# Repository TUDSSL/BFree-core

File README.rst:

BFree Core: Intermittent CircuitPython
-----

This is the intermittent and untethered version of CircuitPython developed jointly by researchers at TU Delft and Northwestern University
-----------

=============

.. image:: https://s3.amazonaws.com/adafruit-circuit-python/CircuitPython_Repo_header_logo.png

|Build Status| |Doc Status| |License| |Discord|

`circuitpython.org <https://circuitpython.org>`__ \| `Get CircuitPython <#get-circuitpython>`__ \|
`Documentation <#documentation>`__ \| `Contributing <#contributing>`__ \|
`Branding <#branding>`__ \| `Differences from Micropython <#differences-from-micropython>`__ \|
`Project Structure <#project-structure>`__

**CircuitPython** is a *beginner friendly*, open source version of Python for tiny, inexpensive
computers called microcontrollers. Microcontrollers are the brains of many electronics including a
wide variety of development boards used to build hobby projects and prototypes. CircuitPython in
electronics is one of the best ways to learn to code because it connects code to reality. Simply
install CircuitPython on a supported board via drag and drop and then edit a ``code.py`` file on
the CIRCUITPY drive. The code will automatically reload. No software installs are needed besides a
text editor (we recommend `Mu <https://codewith.mu/>`_ for beginners.)

CircuitPython features unified Python core APIs and a growing list of 150+ device libraries and
drivers that work with it. These libraries also work on single board computers with regular
Python via the `Adafruit Blinka Library <https://github.com/adafruit/Adafruit_Blinka>`_.

CircuitPython is based on `MicroPython <https://micropython.org>`_. See
`below <#differences-from-micropython>`_ for differences. CircuitPython development is sponsored by
`Adafruit <https://adafruit.com>`_ and is available on their educational development boards. Please
support both MicroPython and Adafruit.

Get CircuitPython
------------------

Official binaries for all supported boards are available through
`circuitpython.org/downloads <https://circuitpython.org/downloads>`_. The site includes stable, unstable and
continuous builds. Full release notes and assets are available through
`GitHub releases <https://github.com/adafruit/circuitpython/releases>`_ as well.

Documentation
-------------

Guides and videos are available through the `Adafruit Learning
System <https://learn.adafruit.com/>`__ under the `CircuitPython
category <https://learn.adafruit.com/category/circuitpython>`__. An API
reference is also available on `Read the Docs
<http://circuitpython.readthedocs.io/en/latest/?>`__. A collection of awesome
resources can be found at `Awesome CircuitPython <https://github.com/adafruit/awesome-circuitpython>`__.

Specifically useful documentation when starting out:

- `Welcome to CircuitPython <https://learn.adafruit.com/welcome-to-circuitpython>`__
- `CircuitPython Essentials <https://learn.adafruit.com/circuitpython-essentials>`__
- `Example Code <https://github.com/adafruit/Adafruit_Learning_System_Guides/tree/master/CircuitPython_Essentials>`__

Contributing
------------

See
`CONTRIBUTING.md <https://github.com/adafruit/circuitpython/blob/master/CONTRIBUTING.md>`__
for full guidelines but please be aware that by contributing to this
project you are agreeing to the `Code of
Conduct <https://github.com/adafruit/circuitpython/blob/master/CODE_OF_CONDUCT.md>`__.
Contributors who follow the `Code of
Conduct <https://github.com/adafruit/circuitpython/blob/master/CODE_OF_CONDUCT.md>`__
are welcome to submit pull requests and they will be promptly reviewed
by project admins. Please join the
`Discord <https://adafru.it/discord>`__ too.

Branding
------------

While we are happy to see CircuitPython forked and modified, we'd appreciate it if forked releases
not use the name "CircuitPython" or the Blinka logo. "CircuitPython" means something special to
us and those who learn about it. As a result, we'd like to make sure products referring to it meet a
common set of requirements.

If you'd like to use the term "CircuitPython" and Blinka for your product here is what we ask:

* Your product is supported by the primary
  `"adafruit/circuitpython" <https://github.com/adafruit/circuitpython>`_ repo. This way we can
  update any custom code as we update the CircuitPython internals.
* Your product is listed on `circuitpython.org <https:/circuitpython.org>`__ (source
  `here <https://github.com/adafruit/circuitpython-org/>`_). This is to ensure that a user of your
  product can always download the latest version of CircuitPython from the standard place.
* Your product has a user accessible USB plug which appears as a CIRCUITPY drive when plugged in.

If you choose not to meet these requirements, then we ask you call your version of CircuitPython
something else (for example, SuperDuperPython) and not use the Blinka logo. You can say it is
"CircuitPython-compatible" if most CircuitPython drivers will work with it.

--------------

Differences from `MicroPython <https://github.com/micropython/micropython>`__
-----------------------------------------------------------------------------

CircuitPython:

-  includes ports for MicroChip SAMD21 (Commonly known as M0 in Adafruit
   product names) and SAMD51 (M4).
-  supports only SAMD21, SAMD51, and nRF52840 ports.
-  tracks MicroPython's releases (not master).
-  floats (aka decimals) are enabled for all builds.
-  error messages are translated into 10+ languages.
-  does not support concurrency within Python (including interrupts and threading). Some concurrency
   is achieved with native modules for tasks that require it such as audio file playback.

Behavior
~~~~~~~~

-  The order that files are run and the state that is shared between
   them. CircuitPython's goal is to clarify the role of each file and
   make each file independent from each other.
-  ``boot.py`` (or ``settings.py``) runs only once on start up before
   USB is initialized. This lays the ground work for configuring USB at
   startup rather than it being fixed. Since serial is not available,
   output is written to ``boot_out.txt``.
-  ``code.py`` (or ``main.py``) is run after every reload until it
   finishes or is interrupted. After it is done running, the vm and
   hardware is reinitialized. **This means you cannot read state from**
   ``code.py`` **in the REPL anymore.** CircuitPython's goal for this
   change includes reduce confusion about pins and memory being used.
-  After ``code.py`` the REPL can be entered by pressing any key. It no
   longer shares state with ``code.py`` so it is a fresh vm.
-  Autoreload state will be maintained across reload.
-  Adds a safe mode that does not run user code after a hard crash or
   brown out. The hope is that this will make it easier to fix code that
   causes nasty crashes by making it available through mass storage
   after the crash. A reset (the button) is needed after its fixed to
   get back into normal mode.
-  RGB status LED indicating CircuitPython state, and errors through a sequence of colored flashes.
-  Re-runs ``code.py`` or other main file after file system writes over USB mass storage. (Disable with
   ``samd.disable_autoreload()``)
-  Entering the REPL after the main code is finished requires a key press which enters the REPL and
   disables autoreload.
-  Main is one of these: ``code.txt``, ``code.py``, ``main.py``,
   ``main.txt``
-  Boot is one of these: ``settings.txt``, ``settings.py``, ``boot.py``,
   ``boot.txt``

API
~~~

-  Unified hardware APIs. Documented
   `on ReadTheDocs <https://circuitpython.readthedocs.io/en/latest/shared-bindings/index.html>`_.
-  API docs are rST within the C files in ``shared-bindings``.
-  No ``machine`` API.

Modules
~~~~~~~

-  No module aliasing. (``uos`` and ``utime`` are not available as
   ``os`` and ``time`` respectively.) Instead ``os``, ``time``, and
   ``random`` are CPython compatible.
-  New ``storage`` module which manages file system mounts.
   (Functionality from ``uos`` in MicroPython.)
-  Modules with a CPython counterpart, such as ``time``, ``os`` and
   ``random``, are strict
   `subsets <https://circuitpython.readthedocs.io/en/latest/shared-bindings/time/__init__.html>`__
   of their `CPython
   version <https://docs.python.org/3.4/library/time.html?highlight=time#module-time>`__.
   Therefore, code from CircuitPython is runnable on CPython but not
   necessarily the reverse.
-  tick count is available as
   `time.monotonic() <https://circuitpython.readthedocs.io/en/latest/shared-bindings/time/__init__.html#time.monotonic>`__

--------------

Project Structure
-----------------

Here is an overview of the top-level source code directories.

Core
~~~~

The core code of
`MicroPython <https://github.com/micropython/micropython>`__ is shared
amongst ports including CircuitPython:

-  ``docs`` High level user documentation in Sphinx reStructuredText
   format.
-  ``drivers`` External device drivers written in Python.
-  ``examples`` A few example Python scripts.
-  ``extmod`` Shared C code used in multiple ports' modules.
-  ``lib`` Shared core C code including externally developed libraries
   such as FATFS.
-  ``logo`` The CircuitPython logo.
-  ``mpy-cross`` A cross compiler that converts Python files to byte
   code prior to being run in MicroPython. Useful for reducing library
   size.
-  ``py`` Core Python implementation, including compiler, runtime, and
   core library.
-  ``shared-bindings`` Shared definition of Python modules, their docs
   and backing C APIs. Ports must implement the C API to support the
   corresponding module.
-  ``shared-module`` Shared implementation of Python modules that may be
   based on ``common-hal``.
-  ``tests`` Test framework and test scripts.
-  ``tools`` Various tools, including the pyboard.py module.

Ports
~~~~~

Ports include the code unique to a microcontroller line and also
variations based on the board.

-  ``atmel-samd`` Support for SAMD21 and SAMD51 based boards.
-  ``nrf`` Support for the nRF52840 based boards.
-  ``unix`` Support for UNIX. Only used for automated testing.

The remaining port directories not listed above are in the repo to maintain compatibility with the
`MicroPython <https://github.com/micropython/micropython>`__ parent project.

`back to top <#circuitpython>`__

.. |Build Status| image:: https://travis-ci.com/adafruit/circuitpython.svg?branch=master
   :target: https://travis-ci.org/adafruit/circuitpython
.. |Doc Status| image:: https://readthedocs.org/projects/circuitpython/badge/?version=latest
   :target: http://circuitpython.readthedocs.io/
.. |Discord| image:: https://img.shields.io/discord/327254708534116352.svg
   :target: https://adafru.it/discord
.. |License| image:: https://img.shields.io/badge/License-MIT-brightgreen.svg
   :target: https://choosealicense.com/licenses/mit/

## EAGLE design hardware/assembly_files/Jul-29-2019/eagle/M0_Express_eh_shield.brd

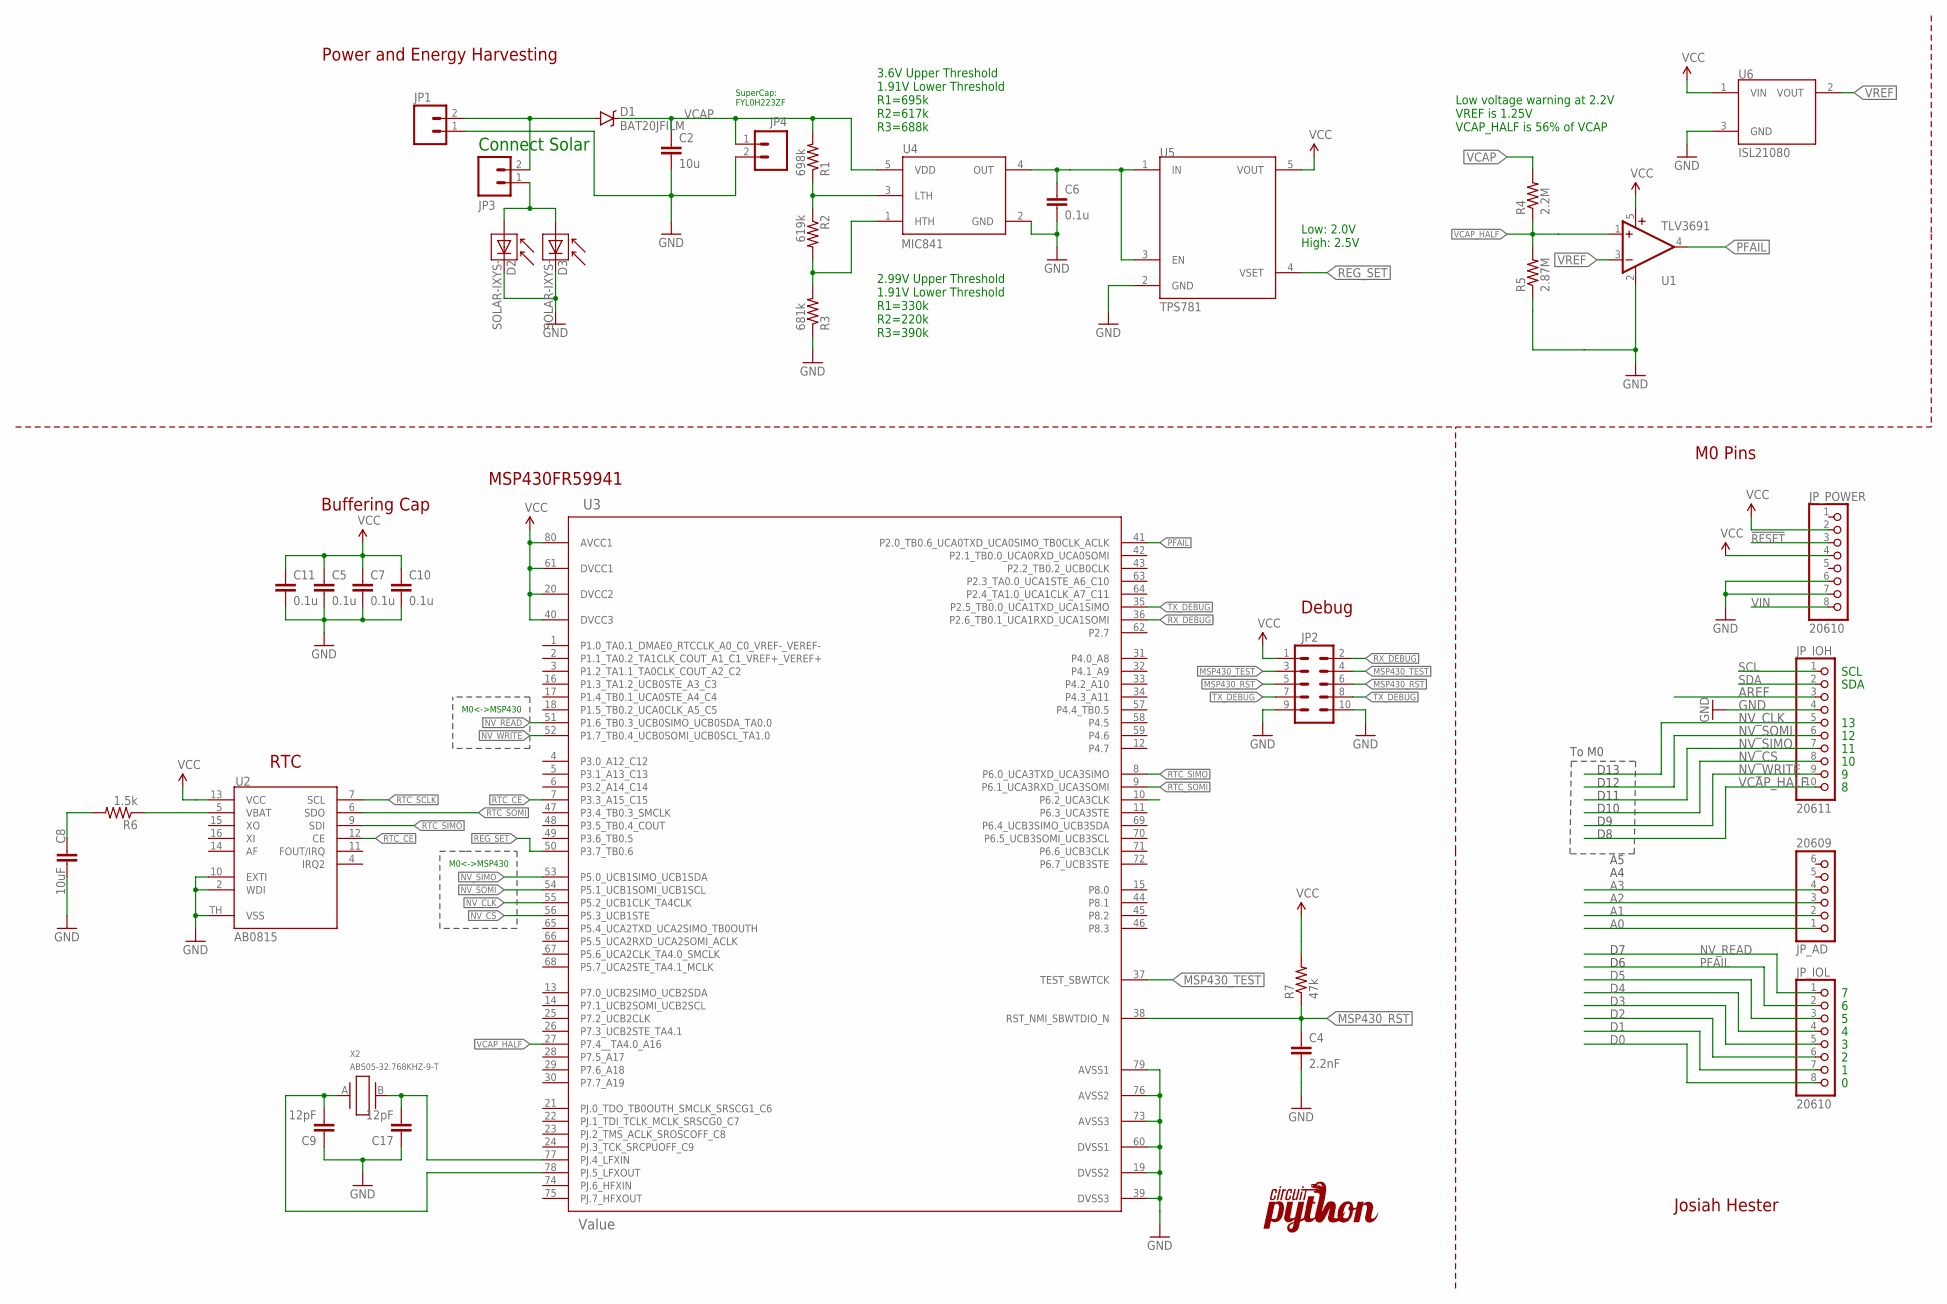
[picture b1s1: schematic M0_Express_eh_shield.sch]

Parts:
C2: 10u; 0805; DIGIKEY 1276-6456-1-ND
C4: 2.2nF; 0603; MPN 06035C222KAT2A; DIGIKEY 478-1219-1-ND
C5, C6, C7, C10, C11: 0.1u; 0603; MPN CL10B104KO8NNNC; DIGIKEY 1276-1005-1-ND
C8: 10uF; 0805; DIGIKEY 1276-6456-1-ND
C9, C17: 12pF; 0603; MPN CL10C120JB8NNNC; DIGIKEY 1276-1254-1-ND
D1: BAT20JFILM; SOD-323; DIGIKEY NSR0530HT1GOSCT-ND
D2, D3: SOLAR-IXYS-; SOLARBIT-12X1; MPN KXOB25-02X8F; DIGIKEY KXOB25-02X8F-ND
JP1, JP3: M02LOCK; 1X02_LOCK
JP2: M05X21.27MM; 2X5_1.27MM; MPN 3220-10-0100-00; DIGIKEY 1175-1627-ND
JP4: M025MM; SCREWTERMINAL-5MM-2
JP_AD: 20609; 1X06_OVALWAVE
JP_IOH: 20611; 1X10_OVALWAVE
JP_IOL: 20610; 1X08_OVALWAVE
JP_POWER: 20610; 1X08_OVALWAVE
R1: 698k; 0603; MPN RC0603FR-07698KL; DIGIKEY 311-698KHRCT-ND
R2: 619k; 0603; MPN RC0603FR-07619KL; DIGIKEY 311-619KHRCT-ND
R3: 681k; 0603; MPN RMCF0603FT681K; DIGIKEY RMCF0603FT681KCT-ND
R4: 2.2M; 0603; MPN RC0603FR-072M2L; DIGIKEY YAG3329CT-ND
R5: 2.87M; 0603; MPN RMCF0603FT2M87; DIGIKEY RMCF0603FT2M87CT-ND
R6: 1.5k; 0603; MPN CRG0603F1K5; DIGIKEY A121524CT-ND
R7: 47k; 0603; MPN CRCW060347K0JNEAC; DIGIKEY 541-4061-1-ND
U1: TLV3691; SC70-5; MPN TLV3691IDCKR; DIGIKEY 296-37910-1-ND
U2: AB0815; QFN16; MPN AB0815-T3
U3: Value; PN0080A_N; DIGIKEY 296-45561-1-ND
U4: MIC841; SC70-5; MPN MIC841HYC5-TR; DIGIKEY 576-2923-1-ND
U5: TPS781; DCK_R-PDSO-G5; DIGIKEY 296-29966-1-ND
U6: ISL21080; SOT-23; MPN ISL21080DIH312Z-TK; DIGIKEY ISL21080DIH312Z-TKTR-ND
U$1: LOGO; CIRCUITPYTHON-LOGO
X2: ABS05-32.768KHZ-9-T; ABS05; MPN ABS05-32.768KHZ-9-T

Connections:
!RESET: JP_POWER.3
A0: JP_AD.1
A1: JP_AD.2
A2: JP_AD.3
A3: JP_AD.4
AREF: JP_IOH.3
D0: JP_IOL.8
D1: JP_IOL.7
D2: JP_IOL.6
D3: JP_IOL.5
D4: JP_IOL.4
D5: JP_IOL.3
GND: C2.2, C4.2, C5.2, C6.2, C7.2, C8.2, C9.1, C10.2, C11.2, C17.1, D2.- (C), D3.- (C), JP1.1, JP2.9, JP2.10, JP4.2, JP_IOH.4, JP_POWER.6, JP_POWER.7, R3.1, R5.1, U1.2 (GND), U2.2 (WDI), U2.10 (EXTI), U2.TH (VSS), U3.19 (DVSS2), U3.39 (DVSS3), U3.60 (DVSS1), U3.73 (AVSS3), U3.76 (AVSS2), U3.79 (AVSS1), U4.2 (GND), U5.2 (GND), U6.3 (GND)
MSP430_RST: C4.1, JP2.5, JP2.6, R7.1, U3.38 (RST_NMI_SBWTDIO_N)
MSP430_TEST: JP2.3, JP2.4, U3.37 (TEST_SBWTCK)
unnamed: D1.A, JP1.2, JP3.2
unnamed: R1.1, R2.1, U4.3 (LTH)
unnamed: R2.2, R3.2, U4.1 (HTH)
unnamed: R6.1, U2.5 (VBAT)
unnamed: C17.2, U3.77 (PJ.4_LFXIN), X2.B (2)
unnamed: C9.2, U3.78 (PJ.5_LFXOUT), X2.A (1)
unnamed: C6.1, U4.4 (OUT), U5.1 (IN), U5.3 (EN)
unnamed: C8.1, R6.2
unnamed: D2.+ (A), D3.+ (A), JP3.1
NV_CLK: JP_IOH.5, U3.55 (P5.2_UCB1CLK_TA4CLK)
NV_CS: JP_IOH.8, U3.56 (P5.3_UCB1STE)
NV_READ: JP_IOL.1, U3.51 (P1.6_TB0.3_UCB0SIMO_UCB0SDA_TA0.0)
NV_SIMO: JP_IOH.7, U3.53 (P5.0_UCB1SIMO_UCB1SDA)
NV_SOMI: JP_IOH.6, U3.54 (P5.1_UCB1SOMI_UCB1SCL)
NV_WRITE: JP_IOH.9, U3.52 (P1.7_TB0.4_UCB0SOMI_UCB0SCL_TA1.0)
PFAIL: JP_IOL.2, U1.4 (OUT), U3.41 (P2.0_TB0.6_UCA0TXD_UCA0SIMO_TB0CLK_ACLK)
REG_SET: U3.50 (P3.7_TB0.6), U5.4 (VSET)
RTC_CE: U2.12 (CE), U3.7 (P3.3_A15_C15)
RTC_SCLK: U2.7 (SCL), U3.10 (P6.2_UCA3CLK)
RTC_SIMO: U2.9 (SDI), U3.8 (P6.0_UCA3TXD_UCA3SIMO)
RTC_SOMI: U2.6 (SDO), U3.9 (P6.1_UCA3RXD_UCA3SOMI)
RX_DEBUG: JP2.2, U3.36 (P2.6_TB0.1_UCA1RXD_UCA1SOMI)
SCL: JP_IOH.1
SDA: JP_IOH.2
TX_DEBUG: JP2.7, JP2.8, U3.35 (P2.5_TB0.0_UCA1TXD_UCA1SIMO)
VCAP: C2.1, D1.C, JP4.1, R1.2, R4.2, U4.5 (VDD)
VCAP_HALF: JP_IOH.10, R4.1, R5.2, U1.1 (+IN), U3.27 (P7.4__TA4.0_A16)
VCC: C5.1, C7.1, C10.1, C11.1, JP2.1, JP_POWER.2, JP_POWER.4, R7.2, U1.5 (V+), U2.13 (VCC), U3.20 (DVCC2), U3.40 (DVCC3), U3.61 (DVCC1), U3.80 (AVCC1), U5.5 (VOUT), U6.1 (VIN)
VIN: JP_POWER.8
VREF: U1.3 (-IN), U6.2 (VOUT)

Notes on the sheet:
SDA
SCL
Josiah Hester
MSP430FR59941
Power and Energy Harvesting
M0 Pins
2.99V Upper Threshold 1.91V Lower Threshold R1=330k R2=220k R3=390k
Low: 2.0V High: 2.5V
M0<->MSP430
D13
D12
D11
D10
RTC
To M0
Connect Solar
Debug
Buffering Cap
3.6V Upper Threshold 1.91V Lower Threshold R1=695k R2=617k R3=688k
Low voltage warning at 2.2V VREF is 1.25V VCAP_HALF is 56% of VCAP
SuperCap: FYL0H223ZF

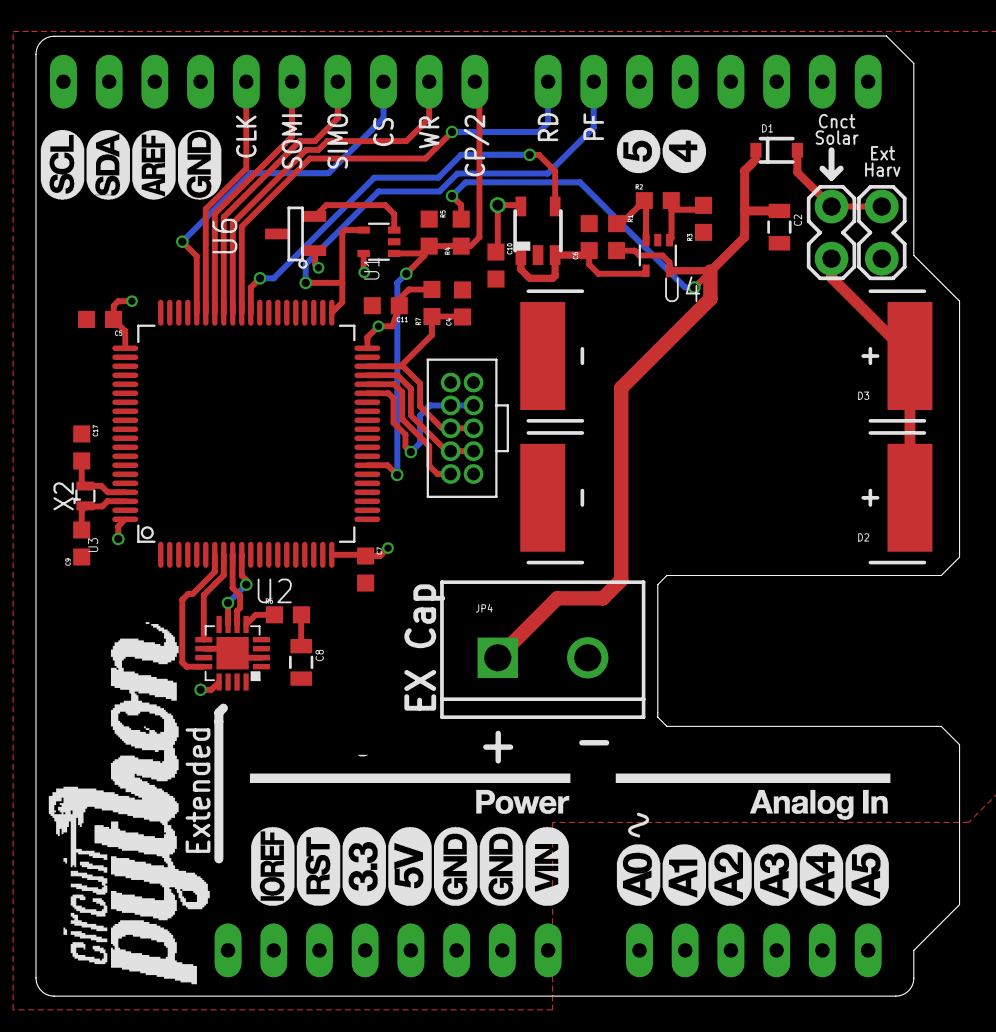
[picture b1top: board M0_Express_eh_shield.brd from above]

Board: 2 copper layers, 51.3 x 53.3 mm, 36 parts (0 on the bottom side), 30 nets.

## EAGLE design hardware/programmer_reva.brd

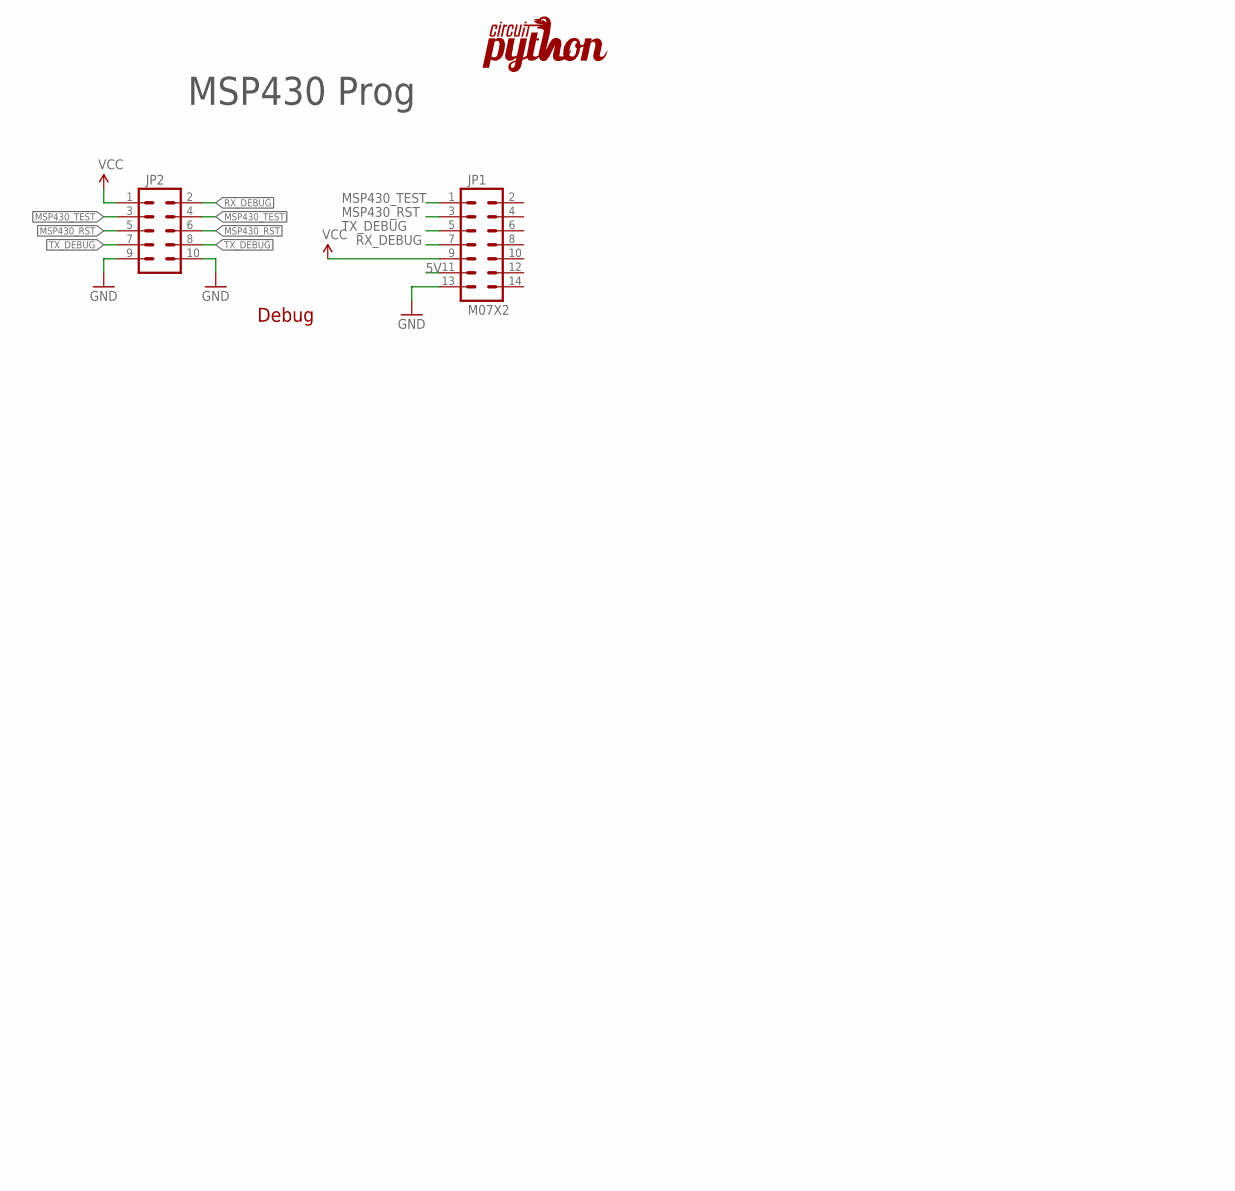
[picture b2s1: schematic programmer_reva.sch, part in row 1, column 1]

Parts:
JP1: M07X2; 2X7
JP2: M05X21.27MM; 2X5_1.27MM; DIGIKEY 1175-1627-ND
U$2: LOGO; CIRCUITPYTHON-LOGO

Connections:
5V: JP1.11
GND: JP1.13, JP2.9, JP2.10
MSP430_RST: JP1.3, JP2.5, JP2.6
MSP430_TEST: JP1.1, JP2.3, JP2.4
RX_DEBUG: JP1.7, JP2.2
TX_DEBUG: JP1.5, JP2.7, JP2.8
VCC: JP1.9, JP2.1

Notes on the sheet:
MCU, Program, Connections
EECS Northwestern University Drawn by Josiah Hester
MSP430 Prog
Debug

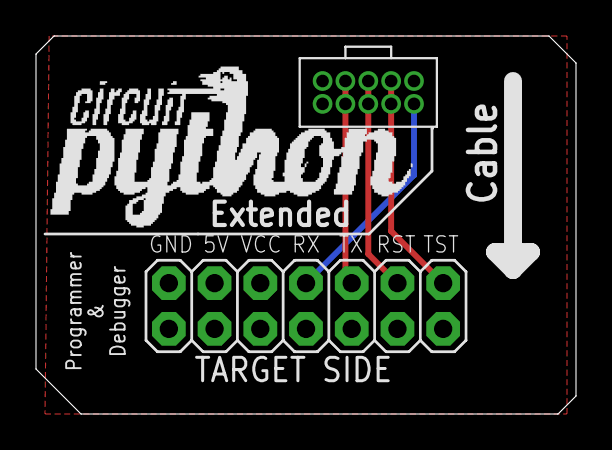
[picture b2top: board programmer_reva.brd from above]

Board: 2 copper layers, 30.0 x 21.0 mm, 4 parts (1 on the bottom side), 6 nets.

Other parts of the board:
U$1: NU-LOGO

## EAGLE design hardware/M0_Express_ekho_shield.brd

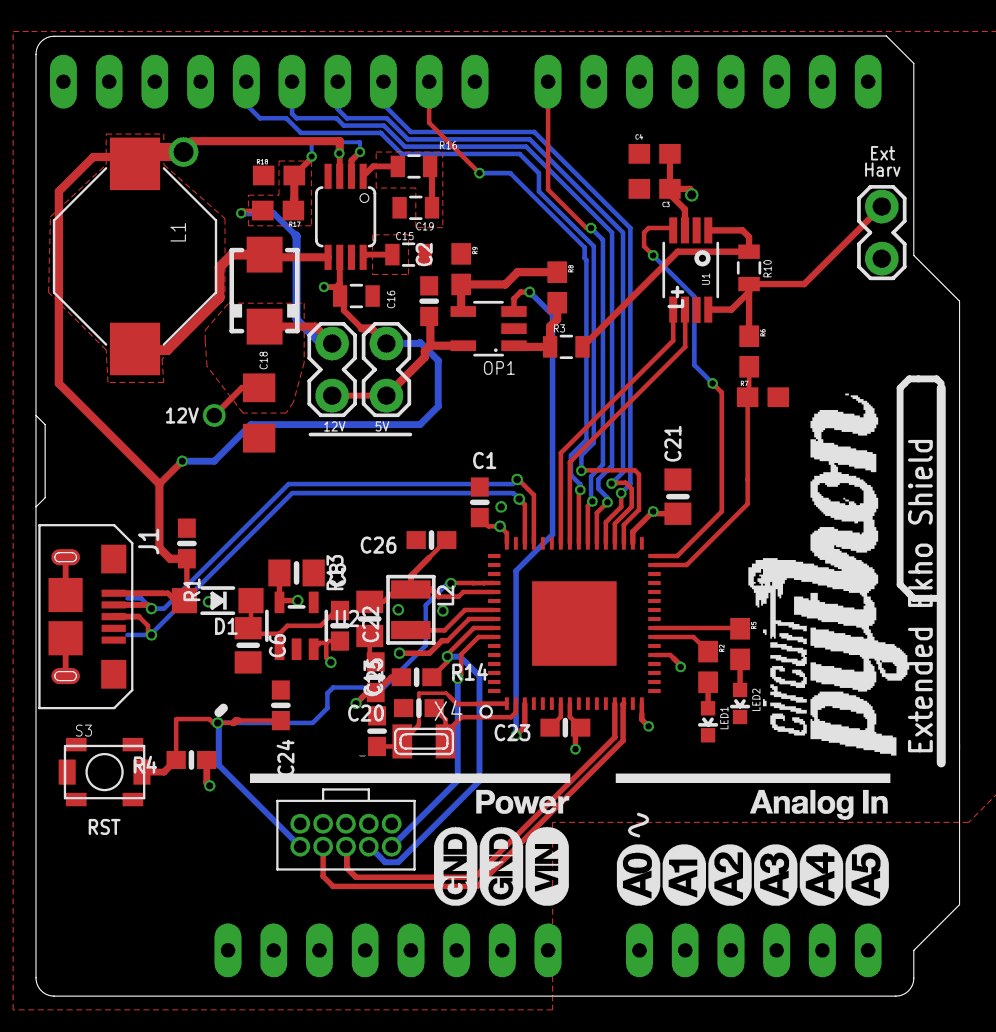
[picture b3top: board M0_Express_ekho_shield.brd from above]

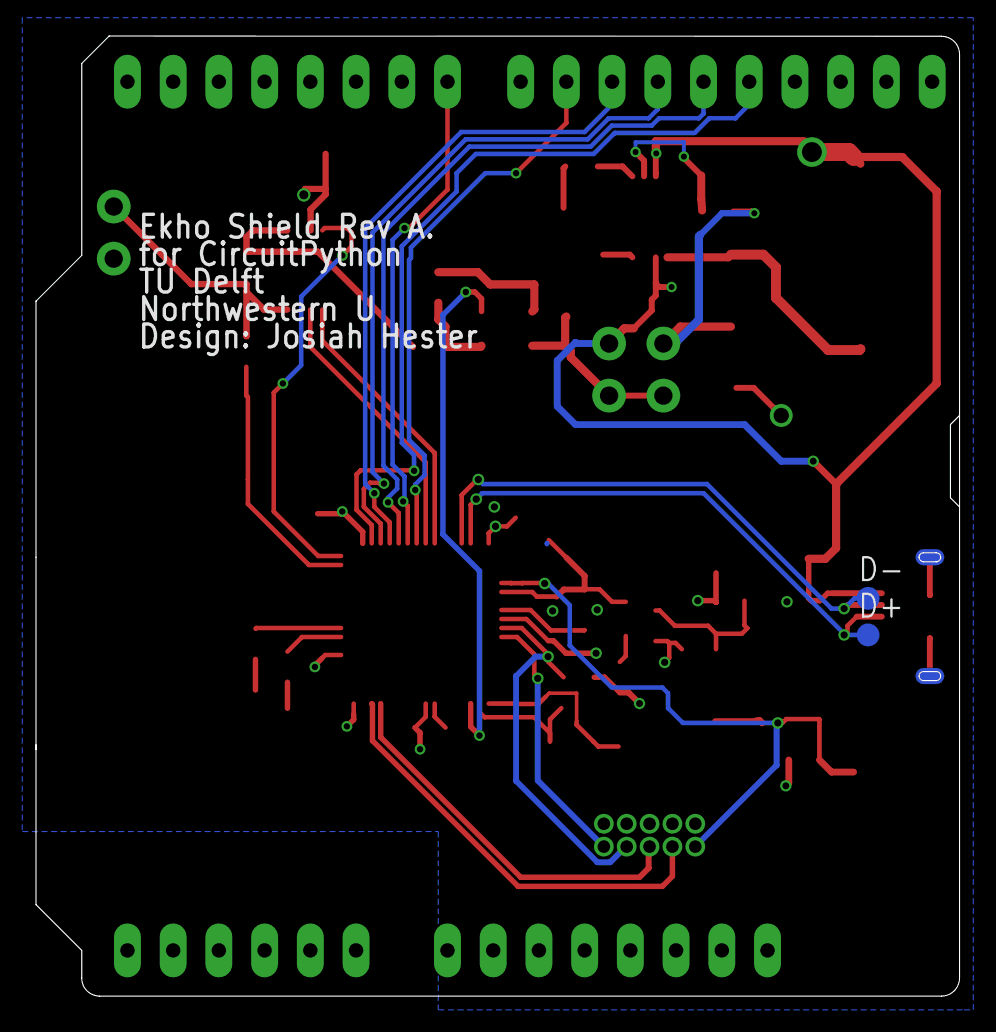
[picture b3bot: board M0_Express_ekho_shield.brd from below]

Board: 2 copper layers, 51.3 x 53.3 mm, 58 parts (2 on the bottom side), 42 nets.

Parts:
C1, C2, C22, C23, C24, C26: 1uF; 0603-NO
C3: 0.1uF; 0603
C4: 1.0uF; 0603
C6, C8: 10µF; 0805-NO
C13, C20: 22pF; 0603-NO
C15: 33nF; 0805
C16: 10uF; 0805
C18: 10uF; 1206
C19: 1000pF; 0805
C21, C25: 10uF; 0805-NO
D1: MBR120; SOD-123
D4: MBRA340T3G; SMA
D+: TPB1,27; B1,27
D-: TPB1,27; B1,27
J1: MF-CON-MICROUSB-RIGHT; MICROUSB-RIGHT
JP1, JP12, JP13: 1X02_LOCK
JP2: 2X5_1.27MM
JP_AD: 20609; 1X06_OVALWAVE
JP_IOH: 20611; 1X10_OVALWAVE
JP_IOL: 20610; 1X08_OVALWAVE
JP_POWER: 20610; 1X08_OVALWAVE
L1: 6.8uH; D03316P
L2: 10uH; INDUCTOR_1007
LED1: red; LED-0603
LED2: green; LED-0603
OP1: LT1797; TSOT23-8
R1, R4, R13, R14: 10K; 0603-NO
R2, R5: 330; 0603
R3: 100; 0805
R6: 3M; 0603
R7: 1M; 0603
R8: 2.2k; 0603
R9: 1k; 0603
R10: 10; 0805
R16: 10k; 0805
R17: 86.6k; 0603
R18: 10k; 0603
S3: TL1015AF; TS1015
U1: INA225; MSOP8
U2: AP2112-3.3; SOT23-5
U9: ADP1613; MSOP08
U$1: LOGO; CIRCUITPYTHON-LOGO
U$14: ATSAMD51J; PQFN64-1
X4: 32.768; XTAL3215

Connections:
12V: C18.1, D4.C, JP12.1, R17.2
!RESET: C24.2, JP2.10, R4.2, S3.2, U$14.52
+3V3: C1.1, C3.1, C4.1, C8.1, C21.1, C22.1, C23.1, JP2.1, R4.1, R14.1, U1.3, U2.5, U$14.8, U$14.16, U$14.21, U$14.34, U$14.48, U$14.56
AVCC_SET: C2.1, JP12.2, JP13.2, OP1.5
CSG0: U1.5, U$14.42
CSG1: U1.6, U$14.41
CS_ADC: U1.4, U$14.32
D+: D+.TP, J1.3, U$14.46
D-: D-.TP, J1.2, U$14.45
EN: R13.1, U2.3
GND: C1.2, C2.2, C3.2, C4.2, C6.2, C8.2, C13.2, C15.2, C16.2, C18.2, C19.2, C20.2, C21.2, C22.2, C23.2, C24.1, C25.2, C26.2, J1.5, J1.S1, J1.S2, J1.S3, J1.S4, J1.S5, J1.S6, JP1.1, JP2.3, JP2.5, JP_IOH.4, JP_POWER.6, JP_POWER.7, LED1.C, LED2.C, OP1.2, R1.1, R7.2, R9.1, R18.1, S3.1, S3.G1, S3.G2, S3.G3, S3.G4, U1.2, U1.7, U2.2, U9.4, U9.7, U$14.7, U$14.22, U$14.33, U$14.47, U$14.54, U$14.EXP
HARVESTER_IN: OP1.1, R3.1, R8.2
HIGH_LOAD_V+: R3.2, R10.1, U1.1
LED1: R2.1, U$14.23
LED2: R5.1, U$14.24
LOW_LOAD_V+: JP1.2, R6.1, R10.2, U1.8
unnamed: OP1.4, R8.1, R9.2
unnamed: C13.1, U$14.1, X4.P$1
unnamed: C20.1, U$14.2, X4.P$2
unnamed: C15.1, U9.8
unnamed: L2.P$2, U$14.55
unnamed: R16.2, U9.1
unnamed: C19.1, R16.1
unnamed: R17.1, R18.2, U9.2
unnamed: LED1.A, R2.2
unnamed: LED2.A, R5.2
NV_CLK: JP_IOH.5, U$14.35
NV_CS: JP_IOH.8, U$14.37
NV_READ: JP_IOL.1, U$14.39
NV_SIMO: JP_IOH.7, U$14.36
NV_SOMI: JP_IOH.6, U$14.38
NV_WRITE: JP_IOH.9, U$14.40
SW: D4.A, L1.P$2, U9.5
SWDCLK: JP2.4, R14.2, U$14.57
SWDIO: JP2.2, U$14.58
TDI/RX_DEBUG: JP2.8, U$14.14
TDO/TX_DEBUG: JP2.6, U$14.13
VBUS: C16.1, D1.A, J1.1, JP13.1, L1.P$1, R1.2, U9.3, U9.6
VDAC: OP1.3, U$14.3
VDDCORE1: C25.1, C26.1, L2.P$1, U$14.53
VHI: C6.1, D1.C, R13.2, U2.1
VS_ADC: R6.2, R7.1, U$14.31

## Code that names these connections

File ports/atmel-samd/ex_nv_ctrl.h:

/**
 * API for sennding and recieving bytes to/from the external Non-volatile memory controller,
 * which is a MSP430FR59941 in the current version.
 * 
 * PIN ASSIGNMENTS  for the Interface to the MSP430.
 * ===============================================
 * CP  |     Function    |  MSP |  M0
 * ===============================================
 * D13 | CLK             | P5.2 | PA17/SERCOM1+3.1
 * D12 | SOMI            | P5.1 | PA19/SERCOM1+3.3
 * D11 | SIMO            | P5.0 | PA16/SERCOM1+3.0
 * D10 | CS              | P5.3 | PA18/SERCOM1+3.2
 * D9  | NV_WRITE / GPIO1| P1.7 | PA07
 * D8  | VCAP_HALF / ADC | P7.4 | PA06
 * D7  | NV_READ         | P1.6 | PA21
 * D6  | PFAIL           | P2.0 | PA20
 * 
 * @author Josiah Hester
 * 
 */
#ifndef EX_NV_CTRL_H
#define EX_NV_CTRL_H

#include <stdint.h>

void _init_nv_interface();

uint8_t write_bytes_to_nv(uint8_t * arr, uint16_t addr);
uint8_t read_bytes_from_nv(uint16_t addr, uint16_t len, uint8_t * target_arr);
uint8_t get_last_checkpoint(uint8_t * target_mem);
uint8_t checkpoint_exists();

#endif |

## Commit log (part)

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2019-07-06 Added dev env stuff and GDB script to ease debugging
2019-07-06 Update to guide
2019-07-18 Add memory region write support
    This is the initial part required to support checkpoints that are stored
    on the PC. This commit adds support for restoring memory regions.
    In the `scripts` directory there is a python script called:
    `restore-mem-serial.py`
    This scripts works in tandem with the added code in main.c (have to move
    it somewhere else).
2019-07-19 Switch to the safe stack before entering restore
    This will be needed when we restore the stack because otherwise we might
    overwrite our current stack frame and that will cause very strange
    bugs.
2019-07-19 Work on python script create a checkpoint and store it
    Not finished
2019-07-22 Add filename support to the checkpoint storage
2019-07-22 Remove the old scripts
    They are merged into checkpoint-serial.py
2019-07-22 Allow for register checkpointing
2019-07-23 Add register restoration etc
    Kinda works for the registers
2019-07-26 finished schematic of the board
2019-07-26 general makefile settings
2019-07-26 updates and programmer
2019-07-29 finished hardware
2019-07-29 Cleanup the assembly, main and usage is still trash
    Copied from the comment in checkpoint_scv.s
    +===================+============================================+
    | *Exception Frame* after entering ISR |
    +===================+============================================+
    | Process stack | <- SP before interrupt |
    +-------------------+--------------------------------------------+
2019-07-30 updated with parts and final silk
2019-07-30 Integrate register checkpoint
2019-07-30 Fix checkpoint-serial python code for on the computer (NVM storage)
    Still shit though
2019-07-30 Improve the NVM code on the computer somewhat
    Having it line-based is a bad idea, change it to character based.
2019-07-31 General cleanup
2019-08-01 Add special linker script files for checkpoint obj
    All objects in .bss and .data that have to be checkpointed (restored)
    should be listed in the special linker script files.
2019-08-03 final hardware files, already sent to fab
2019-08-05 Fix "caching" bug
2019-08-05 Make a simple restore example
    Reset is done in gdb with `monitor reset`
    Add an ugly retry to `checkpoint-serial.py` because USB is reset
2019-08-05 Add retry to restore request
    Remove the long delay in main.c that was there to make sure the NVM
    serial connected was up before requesting the retstore.
    TODO: Make it more robust, now random data can crash it
2019-08-05 Add garbage collection memory to the checkpoint
    NB. Not tested
2019-08-06 Add quiet option to checkpoint-serial.py
2019-08-06 Disable garbage collector checkpoint
    It is not working correctly over USB
    When I try to restore the checkpoint the data send is probably to much
    and the USB FIFO seems to get messed up.
    Because we will move away from USB I don't want to spend time fixing it.
    Because it's not in the .data or .bss section it is OK to ignore and act
    as if it was restored correctly.
2019-08-06 Make the memory diff a bit less source line dependent
    It now breaks on the restore point check in`checkpoint.c`
    `gdb-memory-diff-dump.py` checks the actual value of
    `checkpoint_svc_restore` to see if it was a checkpoint or restore.
    On a checkpoint it overwrites the `after-cp` memory dump.
    On a restore it overwrites the `after-restore` memory dump and compares
    them.
2019-08-07 Remove unused function
2019-08-07 schematic and partial board layout for CP-intermittent Ekho
2019-08-08 final schematic
2019-08-08 final ekho hardware done
2019-08-09 write to mem method verified
2019-08-12 can measure current and communicate/takeover the M0 kind of like a debugger
2019-08-23 [WIP] Metro checkpoint code for NVM communication
    Not fully working, has communication error on restore
2019-08-26 [WIP/BUG] Metro/Sam SPI DMA read only does 15 bytes
    Write is working, don't yet know what the problem is.
2019-08-26 [Bugfix] Cast the variable to the address
    The variable holds the destination address, this should be cast to
    pointer instead of taking the address of the variable.
2019-08-27 Naive sync
    Need to improve synchronisation.
    This is a WIP and is a bit to sketchy. Commit it to not loose it if it
    turns out I do need it later.
2019-08-27 Fix synchronisation
2019-08-27 Cleanup
2019-08-27 Extra read is required
    Reverse of commit 965a5249433d1c1666fc5c122770aad1ed16f1b3
2019-09-02 Fix pesky off by one bug, caused by DMA
    Because I added an OR instead of just writing the register, whenever we
    first use the DMA write, the following DMA reads will be miss configured
    causing a shift of one byte in the received data.
2019-09-02 Correct restore stack location
    Should not make a difference
2019-09-02 Remove breakpoint variables from vm.c
2019-09-02 Add reset command to GDB load script
2019-09-02 Cleanup main.c
2019-09-02 Change GDB verification trigger
    NB. Messy version that triggers before the register restore.
    Will clean it up when the NVM is fully debugged, otherwise Hard faults
    can happen before we diff the memory :(
    Add the dummy function `gdb_break_me()` function.
    The primary use of this function if to make it easy for GDB to break on.
    Otherwise we need to specify a line number, which can be messy if the
2019-09-02 Enable Garbage collection checkpoint
2019-09-02 Remove legacy SPI example code from `main.c`
2019-09-02 Move NVM debug print definitions and config
2019-09-04 Add NVM clear command
    Not tested and never used. Need to integrate it with the reset procedure
    in circuitpython.
2019-09-04 Add safe_mode enum for USER_RESET
    At default the safe_mode is set to USER_RESET instead of NO_SAFE_MODE
    This means that when the system reboots because of the reset button it
    will see this as RAM state is not lost.
    Whenever a "fresh" boot is done (power was lost) the system will return
    NO_SAFE_MODE.
    When there is a USER_RESET CircuitPython will send a checkpoint_delete()
2019-09-12 Increase number of checkpoint segments to 16
2019-09-12 [nvm] add address print to debug
2019-09-12 Add microtracebffer gdb script
    From: https://github.com/adafruit/gdb-micro-trace-buffer
    Changed to work with python 3
2019-09-12 [GDB] Add automatic memory range support
    Instead of manually adding the address ranges it now automatically gets
    them.
2019-09-13 Basic I2C restoration
    Restores the I2C peripheral (register setup, sercom etc)
    Not intensely tested
    Python code used to test:
    ```
    import board
    import busio
2019-09-13 commented some code to reduce boot time and energy
2019-09-15 Make version where reset is done trough the reset pin
2019-09-16 Add memory barrier
    Not having the memory barrier caused a HardFault (I think).
    Sounds reasonable.
    Also removed the instruction "barrier" from the restore as it's never
    called (restore just jumps at the end to the stored PC).
2019-09-16 Increase the SPI frequency to 2MHz
    Seems to be the highest stable one.
    It should be able to go up to like 8MHz, don't know why it doesn't work.
    Haven't looked into it yet.
2019-09-17 Make reload code work
    Will now delete checkpoint and run
2019-09-18 Fix NVM delete bug
2019-09-19 created a branch of pc-checkpoint and added IO checkpointing support
2019-09-19 time division implemented
2019-09-19 minor edits
2019-09-20 exclude pinsused in checkpointing protocol
2019-09-20 Remove name
2019-12-09 GDB debug script with vm hook
2019-12-09 Add GDB start scripts
2020-01-23 added checkpointing support for inputs, need to debug
2020-02-07 Add per byte synchronization
    Sometimes the MSP is too slow to read the address values when they are
    send in bulk. So now we synchronize these transactions per byte.
    NB. This means that every NON-DMA transaction now is synchronized per
    byte (by the MSP ready WR signal to the Metro).
    If we observe that the DMA transaction speed is also affected we have a
    bigger problem though. But that does not seem to be the case as of now.
2020-02-07 Reset the NVM controller if garbage is received
2020-02-07 Increase the NVM reset pulse length
    Just to be sure
2020-02-07 Add rudimentary JIT checkpoint Makes it so you can set a checkpoint pending. Now it's set pending every 500ms. But in the future this should be connected to the capacitor voltage level.
2020-02-07 Make the NVM send garbage (42) and hang when a error state is reached
    The Metro board will eventually reset it. We don't want it to randomly
    corrupt checkpoints or something weird.
2020-02-07 Add hook variables for my GDB test script
    Not used in the code, just to break on without changing the stack
    pointer.
2020-02-07 Update GDB test script
    Should fix the way continues are send, as this will eventually give a
    stack overflow in GDB. But that requires a lot of rewrites for which I
    do not have time now :(
2020-02-07 [hacky/todo] Disable boot output file
    Need to do it in the intended way with the #define but I don't yet know
    if that changes other stuff. Will check later.
2020-02-07 Add checkpoint pending and commit print options
    Useful for debugging
2020-02-10 fixed bug in sleep's checkpointing logic
2020-02-11 Move checkpoint period config to header file
2020-02-11 Add checkpoint delay compensation
    Add code that divides the delay amount into set chunk sizes.
    Track the time it takes to perform the checkpoint and subtract it
    from the remaining delay time.
    Making the NV_TIME_DELAY_CHUNK_SIZE_MS smaller increases the checkpoint
    responsiveness, but if it's too low the delay accuracy might go down.
2020-02-12 Add JIT checkpointing when PFail goes high
    3 checkpoint startegies/schedulers are implemented. These can be
    configured in checkpoint.h with the defines:
    ```
    CHECKPOINT_SCHEDULE_TIME_BASED (1)
    CHECKPOINT_SCHEDULE_CAP_SIGNAL_BASED (0)
    CHECKPOINT_SCHEDULE_CAP_SIGNAL_TIME_HYBRID_BASED (0)
2020-02-13 Change ifdef to if in preprocessor
    Stupid, now they weren't disabled
2020-02-15 adding benchmarks
2020-02-15 benchmarks
2020-06-10 Update data, keeps modifying line ending I think
    Hope this does not break it
2020-06-10 Add some debug options
2020-06-10 Disable USB MIDI build
2020-06-10 Disable debug printers by default (as shoudl be the case)
2020-06-15 [checkpoit-asm] Flush cache after restore (and checkpoint)
2020-06-15 [checkpoint] Move peripheral restore to a single file
2020-06-30 [nvm-controller] Add "clear" button (new shield version)
2020-06-30 [scripts] Add helper development scripts
2020-07-07 [checkpoint] Add python bindings to enable/disable checkpoints
2020-07-10 [EPD] Change reset delay to use loop, delay_ms is acting strange
    * NB Untested iterations
2020-07-10 [SPI] Add SPI restore method
2020-07-21 [nvm-controller] Change port setting that enables power rail
2020-07-21 [checkpoint] Disable SPI restore for flash and nvm-controller
    These systems are reinitialised at every boot
2020-07-21 [checkpoint] Add checkpoint python config lib and strategies
    Add configurable checkpoint strategies and period that can be
    configured trough python (import checkpoint)
    NB. Did not yet check all the configuration possibilities.
2020-07-21 [checkpoint] Change nvm-controller speed from 2MHz -> 3MHz
2020-08-13 [checkpoint] Some fixes

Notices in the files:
parts and their libraries:
microbuilder: This work is placed in the public domain, and may be freely used for commercial and non-commercial work with the following conditions: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
SparkFun-Capacitors: Licensing: Creative Commons ShareAlike 4.0 International - https://creativecommons.org/licenses/by-sa/4.0
